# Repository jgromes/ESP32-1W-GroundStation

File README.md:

# ESP32-1W-GroundStation
ESP32-based LoRa ground station

## Features:
* Fully compatible with https://github.com/G4lile0/ESP32-OLED-Fossa-GroundStation
* Radio: Ebyte E22-400M30S (http://www.ebyte.com/en/product-view-news.aspx?id=454)
  * SX1268 with TCXO
  * 1W external PA
  * Automatic Rx/Tx switching
  * IPX and SMA connectors
* OLED display
* Selectable power source (USB/external jack)
* Status LEDs: power, Rx/Tx, ESP32 IO2
* On-board USB/UART convertor

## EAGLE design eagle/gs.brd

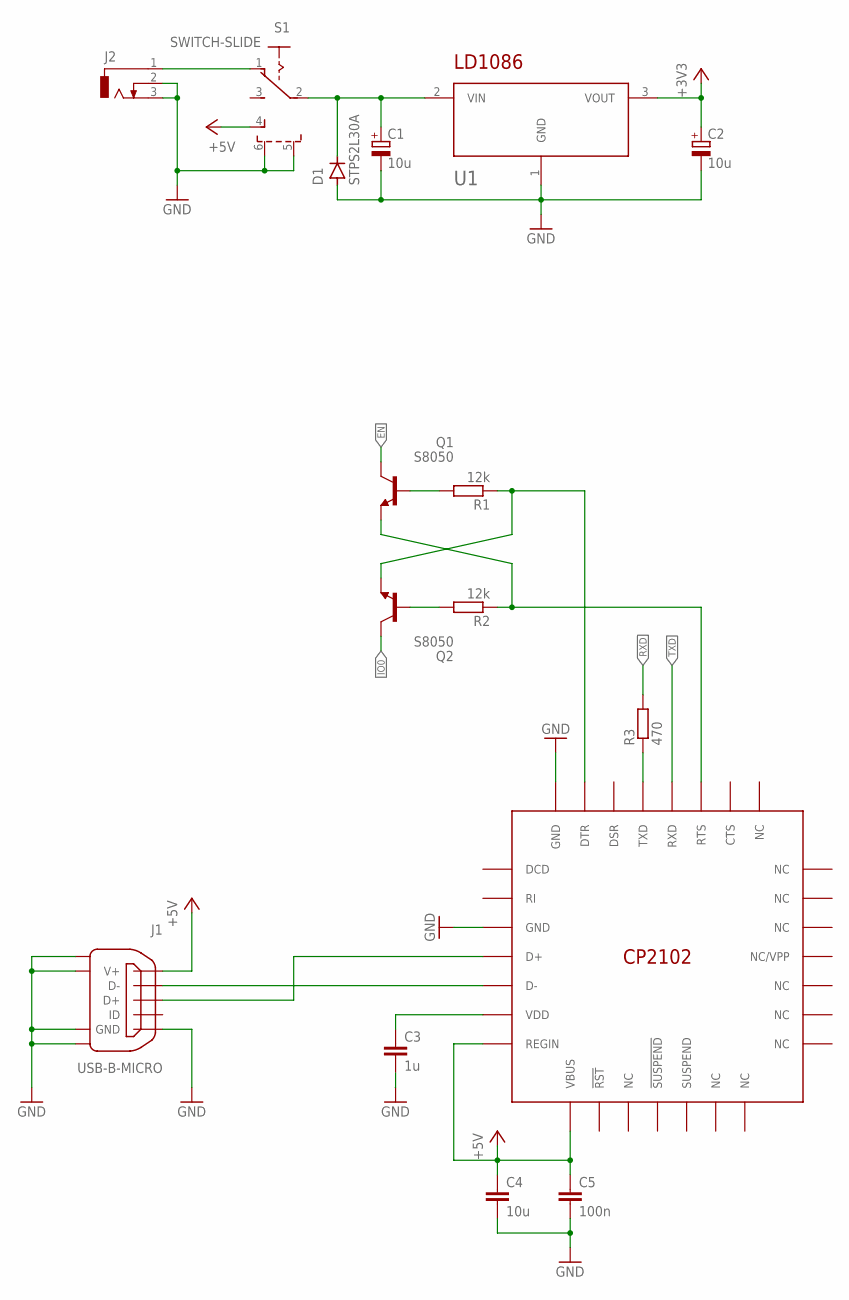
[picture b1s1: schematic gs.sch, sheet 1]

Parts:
C1, C2: 10u; SMC_C
C3: 1u; C0805
C4: 10u; C0805
C5: 100n; C0805
D1: STPS2L30A; DIOM4225X245N
J1: USB-B-MICRO
J2: DCJ0303
Q1, Q2: S8050; SOT95P237X110-3N
R1, R2: 12k; R0805
R3: 470; R0805
S1: SWITCH-SLIDE
U1: LD1086DT33TR; TO228P972X240-3N
U2: CP2102; QFN50P500X500X100-29T300N

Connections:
+3V3: C2.+, U1.3 (VOUT); also elsewhere on the board
+5V: C4.1, C5.1, J1.1 (V+), S1.4, U2.7 (REGIN), U2.8 (VBUS)
EN: Q1.3 (C); also elsewhere on the board
GND: C1.-, C2.-, C3.2, C4.2, C5.2, D1.2 (A), J1.5 (GND), J1.6, J1.7, J1.8, J1.9, J2.2, J2.3, S1.5 (S1), S1.6 (S2), U1.1 (GND), U2.3 (GND), U2.29 (GND); also elsewhere on the board
IO0: Q2.3 (C); also elsewhere on the board
unnamed: J1.2 (D-), U2.5 (D-)
unnamed: J1.3 (D+), U2.4 (D+)
unnamed: R3.1, U2.26 (TXD)
unnamed: Q1.1 (B), R1.2
unnamed: Q2.1 (B), R2.2
unnamed: Q2.2 (E), R1.1, U2.28 (DTR)
unnamed: Q1.2 (E), R2.1, U2.24 (RTS)
unnamed: C3.1, U2.6 (VDD)
unnamed: J2.1, S1.1
unnamed: C1.+, D1.1 (C), S1.2, U1.2 (VIN)
RXD: R3.2; also elsewhere on the board
TXD: U2.25 (RXD); also elsewhere on the board

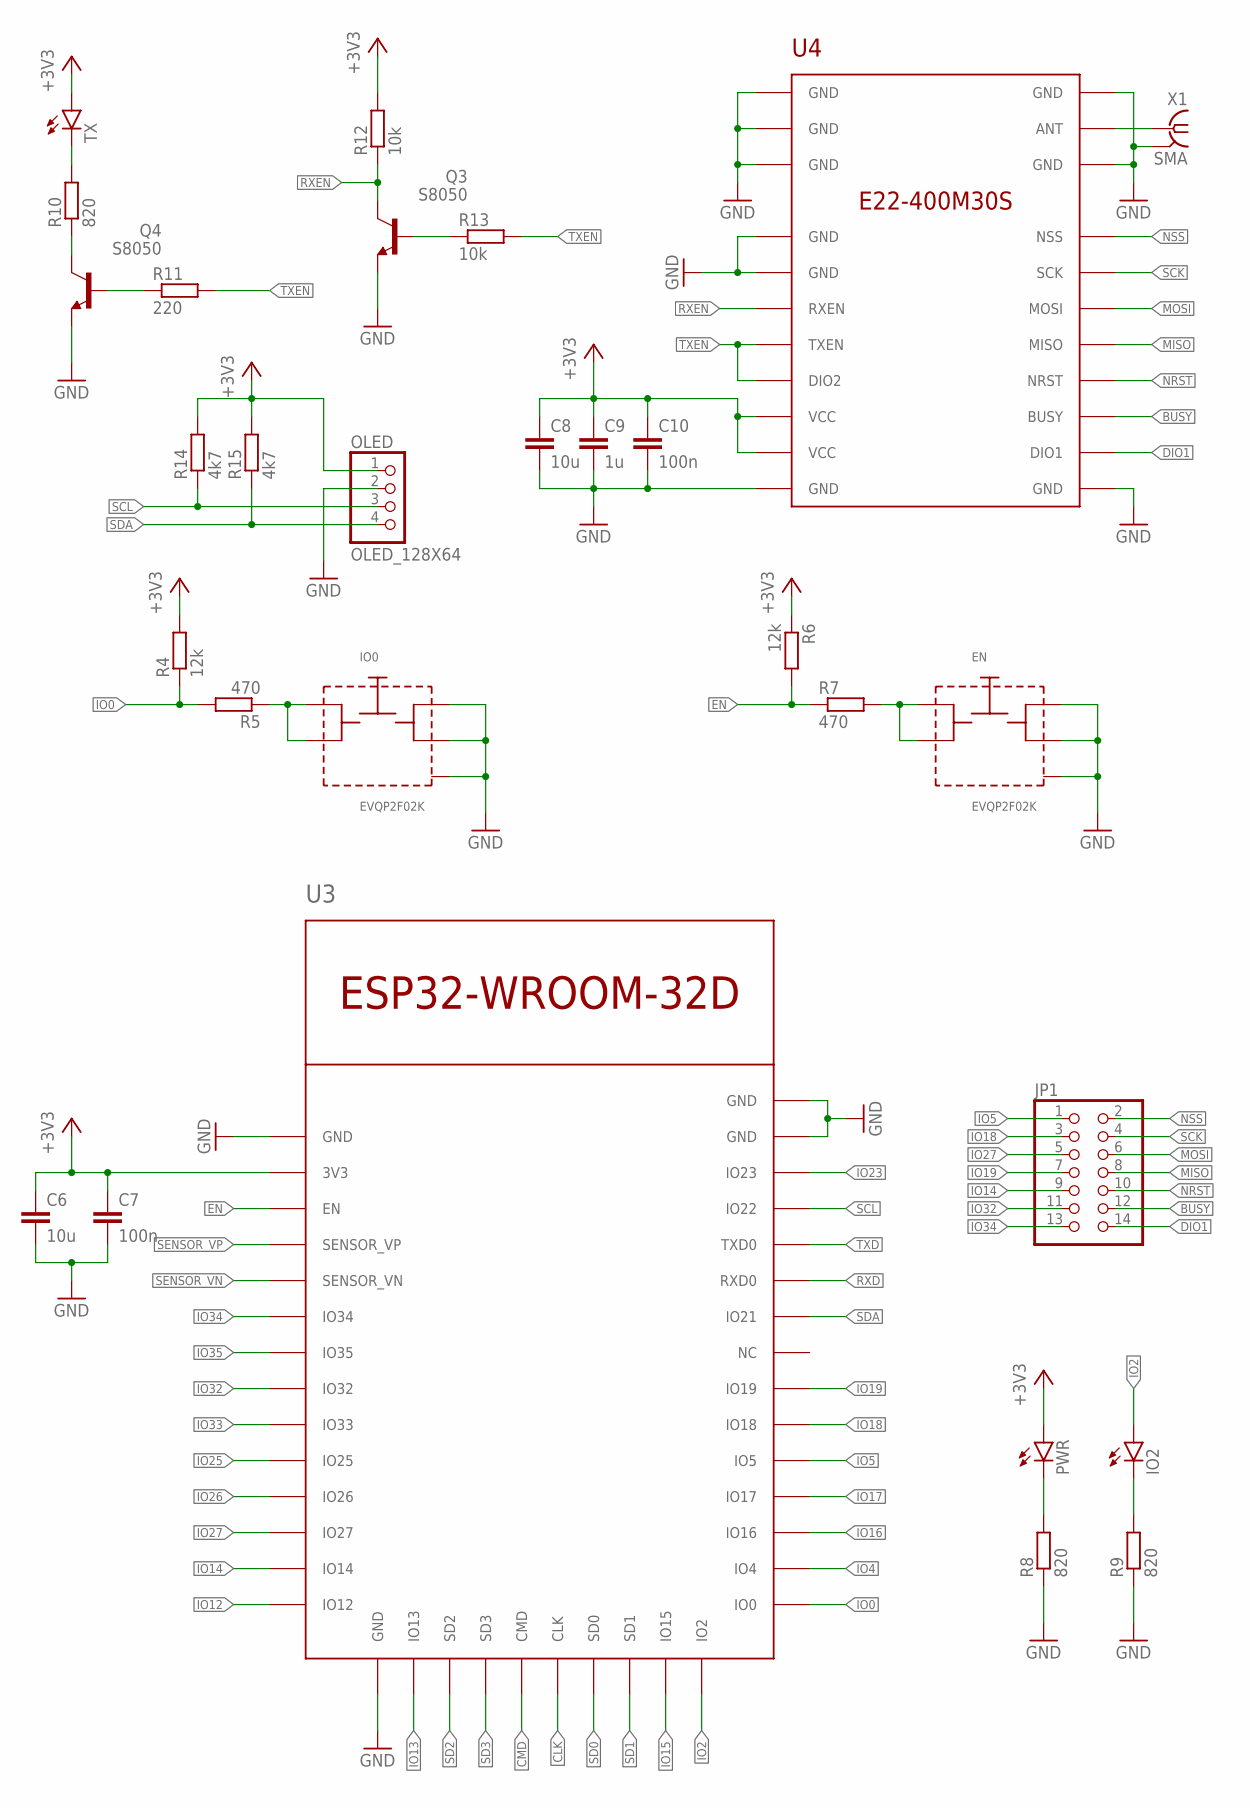
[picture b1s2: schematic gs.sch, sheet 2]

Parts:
C6, C8: 10u; C0805
C7, C10: 100n; C0805
C9: 1u; C0805
EN: EVQP2F02K
IO0: EVQP2F02K
IO2: LEDCHIP-LED0805; CHIP-LED0805
JP1: PINHD-2X7; 2X07
OLED: OLED_128X64
PWR: LEDCHIP-LED0805; CHIP-LED0805
Q3, Q4: S8050; SOT95P237X110-3N
R4, R6: 12k; R0805
R5, R7: 470; R0805
R8, R9, R10: 820; R0805
R11: 220; R0805
R12, R13: 10k; R0805
R14, R15: 4k7; R0805
TX: LEDCHIP-LED0805; CHIP-LED0805
U3: ESP32-WROOM-32D; ESP32-SOLO-1
U4: E22-400M30S
X1: SMA

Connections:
+3V3: C6.1, C7.1, C8.1, C9.1, C10.1, OLED.1, PWR.A, R4.2, R6.1, R12.2, R14.2, R15.2, TX.A, U3.2 (3V3), U4.9 (VCC), U4.10 (VCC); also elsewhere on the board
BUSY: JP1.12, U4.14 (BUSY)
CLK: U3.20 (CLK)
CMD: U3.19 (CMD)
DIO1: JP1.14, U4.13 (DIO1)
EN: R6.2, R7.1, U3.3 (EN); also elsewhere on the board
GND: C6.2, C7.2, C8.2, C9.2, C10.2, EN.3, EN.4, EN.5, IO0.3, IO0.4, IO0.5, OLED.2, Q3.2 (E), Q4.2 (E), R8.1, R9.1, U3.1 (GND), U3.15 (GND), U3.38 (GND), U3.39 (GND), U4.1 (GND), U4.2 (GND), U4.3 (GND), U4.4 (GND), U4.5 (GND), U4.11 (GND), U4.12 (GND), U4.20 (GND), U4.22 (GND), X1.G@1 (2), X1.G@2 (2), X1.G@3 (2), X1.G@4 (2); also elsewhere on the board
IO0: R4.1, R5.2, U3.25 (IO0); also elsewhere on the board
IO2: IO2.A, U3.24 (IO2)
IO4: U3.26 (IO4)
IO5: JP1.1, U3.29 (IO5)
IO12: U3.14 (IO12)
IO13: U3.16 (IO13)
IO14: JP1.9, U3.13 (IO14)
IO15: U3.23 (IO15)
IO16: U3.27 (IO16)
IO17: U3.28 (IO17)
IO18: JP1.3, U3.30 (IO18)
IO19: JP1.7, U3.31 (IO19)
IO23: U3.37 (IO23)
IO25: U3.10 (IO25)
IO26: U3.11 (IO26)
IO27: JP1.5, U3.12 (IO27)
IO32: JP1.11, U3.8 (IO32)
IO33: U3.9 (IO33)
IO34: JP1.13, U3.6 (IO34)
IO35: U3.7 (IO35)
MISO: JP1.8, U4.16 (MISO)
MOSI: JP1.6, U4.17 (MOSI)
unnamed: PWR.C, R8.2
unnamed: IO2.C, R9.2
unnamed: EN.1, EN.2, R7.2
unnamed: IO0.1, IO0.2, R5.1
unnamed: U4.21 (ANT), X1.1
unnamed: Q4.3 (C), R10.1
unnamed: Q3.1 (B), R13.1
unnamed: Q4.1 (B), R11.1
unnamed: R10.2, TX.C
NRST: JP1.10, U4.15 (NRST)
NSS: JP1.2, U4.19 (NSS)
RXD: U3.34 (RXD0); also elsewhere on the board
RXEN: Q3.3 (C), R12.1, U4.6 (RXEN)
SCK: JP1.4, U4.18 (SCK)
SCL: OLED.3, R14.1, U3.36 (IO22)
SD0: U3.21 (SD0)
SD1: U3.22 (SD1)
SD2: U3.17 (SD2)
SD3: U3.18 (SD3)
SDA: OLED.4, R15.1, U3.33 (IO21)
SENSOR_VN: U3.5 (SENSOR_VN)
SENSOR_VP: U3.4 (SENSOR_VP)
TXD: U3.35 (TXD0); also elsewhere on the board
TXEN: R11.2, R13.2, U4.7 (TXEN), U4.8 (DIO2)

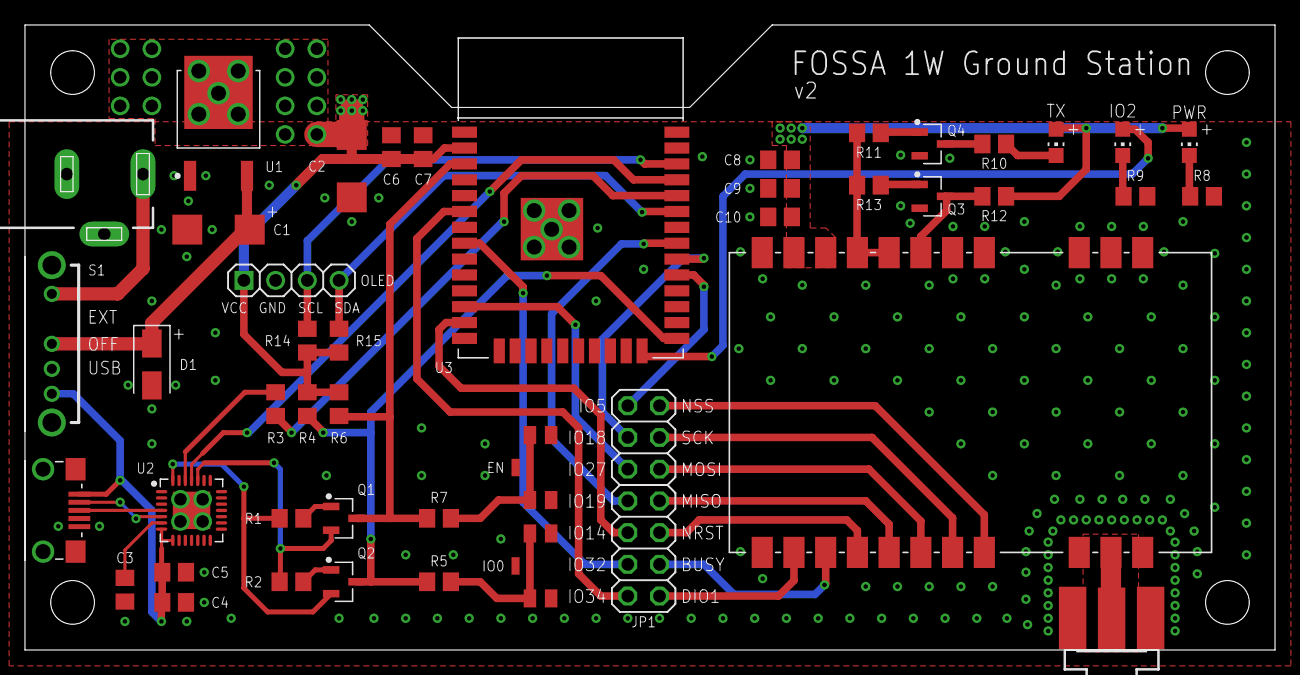
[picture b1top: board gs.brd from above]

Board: 2 copper layers, 100.1 x 50.0 mm, 45 parts (0 on the bottom side), 45 nets.

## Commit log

2020-12-17 Added gitignore
2020-12-17 Added v2 Eagle files + Gerbers
2020-12-17 Added photos
2021-01-21 Fixed ESP32-SOLO-1 used instead of ESP32-WROOM-32D
2021-01-24 Added schematic as PDF
